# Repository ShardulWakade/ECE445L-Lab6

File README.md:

# Lab 6 Introduction to PCB Design

## Table of Contents

- [Lab 6 Introduction to PCB Design](#lab-6-introduction-to-pcb-design)
  - [Table of Contents](#table-of-contents)
  - [0 Repository Structure](#0-repository-structure)
    - [0.1 HW](#01-hw)
    - [0.2 SW](#02-sw)
    - [0.3 Resources](#03-resources)
    - [0.4 Git and Github](#04-git-and-github)
---

## 0 Repository Structure

The typical explanation for the repo structure. Lab specific instructions can be
found further below.

### 0.1 HW

The `hw` folder should contain your schematic and board files for your PCB or
circuits. In labs 1-5 and 10, you will be creating schematics for your circuit
in EAGLE. A setup tutorial can be found
[here](https://www.shawnvictor.net/autodesk-eagle.html).

### 0.2 SW

The `sw` folder should contain your application firmware and software written
for the lab. The `sw/inc` folder contains firmware drivers written for you by
Professor Valvano. Feel free to write your own (in fact, in some labs, you may
be required to write your own).

You can place any other source files in the `sw` folder. TAs will look at the
files you create and/or modify for software quality and for running your
project.

### 0.3 Resources

A couple files are provided in the Resources folder so you don't have to keep
searching for that one TI document. Some of them are immediately useful, like
the TM4C datasheet. Others may be useful for your final project, like the
TM4C_System_Design_Guidelines page.

### 0.4 Git and Github

We will extensively use Git and Github for managing lab projects. This makes it
easier for TAs to grade and help debug the project by allowing us to see commit
histories, maintain a common project structure, and likewise, it makes it easier
for students to collaborate with partners, merge different codebases, and to
debug their work by having a history of commits.

Two common ways of using Git and Github are [Github Desktop](https://desktop.github.com/) and the [command line](https://git-scm.com/downloads).
[Tutorials](https://dev.to/mollynem/git-github--workflow-fundamentals-5496) are also abundant on the net for you to peruse. We've provided a cheatsheet for git
in the Resources folder.

It is highly recommended to make the most out of Git, even if you've never used
it before. Version control will save you a lot of suffering, and tools like Git
or SVN are ubiquitous in the industry.

A gitignore file is added to the root of this repo that may prevent specific
files from being tagged to the repo. This are typically autogenerated output
files we don't care about, but sometimes other stuff (like .lib files) falls
through that we want. Feel free to modify if necessary.

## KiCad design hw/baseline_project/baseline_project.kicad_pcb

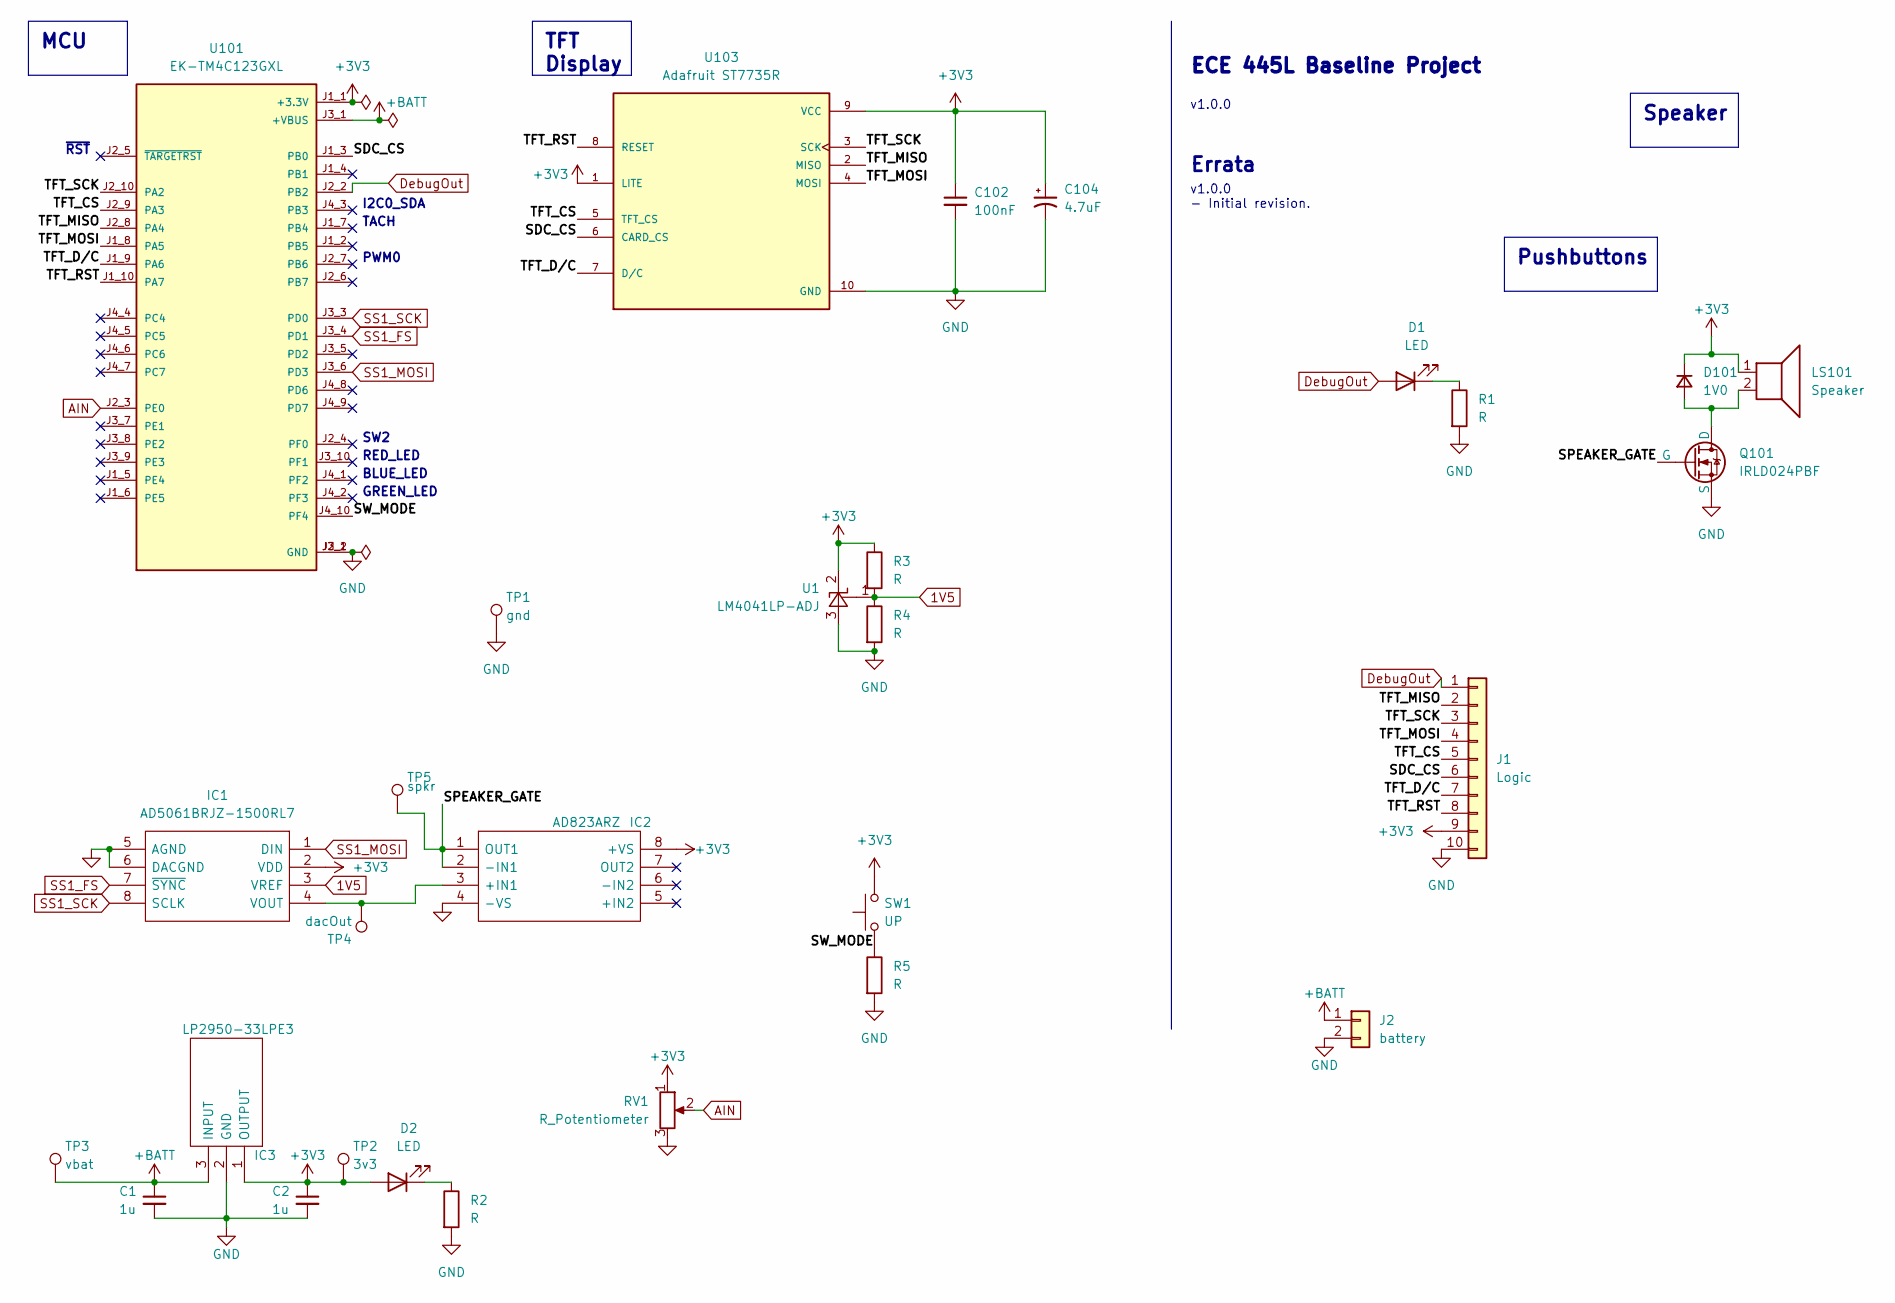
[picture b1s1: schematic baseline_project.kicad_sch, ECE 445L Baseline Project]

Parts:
C1, C2: 1u; C_1206_3216Metric
C102: 100nF; C_Axial_L5.1mm_D3.1mm_P15.00mm_Horizontal
C104: 4.7uF; CP_Axial_L10.0mm_D4.5mm_P15.00mm_Horizontal
D1, D2: LED; LED_D5.0mm
D101: 1V0; D_5W_P12.70mm_Horizontal
IC1: AD5061BRJZ-1500RL7; SOT65P280X145-8N; Mouser Part Number 584-AD5061BRJZ1500R7
IC2: AD823ARZ; SOIC127P600X175-8N; Mouser Part Number 584-AD823ARZ
IC3: LP2950-33LPE3; TO127P419X482X788-3P; Mouser Part Number 595-LP2950-33LPE3
J1: Logic; PinHeader_1x10_P2.54mm_Vertical
J2: battery; PinHeader_1x02_P2.54mm_Vertical
LS101: Speaker; PinHeader_1x02_P2.54mm_Vertical
Q101: IRLD024PBF; vishay_IRLD024PBF
R1, R2, R3, R4, R5: R; R_Axial_DIN0411_L9.9mm_D3.6mm_P12.70mm_Horizontal
RV1: R_Potentiometer; Potentiometer_Bourns_PTA3043_Single_Slide
SW1: UP; SW_PUSH_6mm
TP1: gnd; TestPoint_Bridge_Pitch7.62mm_Drill1.3mm
TP2: 3v3; TestPoint_Bridge_Pitch7.62mm_Drill1.3mm
TP3: vbat; TestPoint_Bridge_Pitch7.62mm_Drill1.3mm
TP4: dacOut; TestPoint_Bridge_Pitch7.62mm_Drill1.3mm
TP5: spkr; TestPoint_Bridge_Pitch7.62mm_Drill1.3mm
U1: LM4041LP-ADJ; TO-92_Inline
U101: EK-TM4C123GXL; ti_EKTM4C123GXL
U103: Adafruit ST7735R; adafruit_st7735r

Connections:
1V5: IC1.3 (VREF), R3.2, R4.1, U1.1 (FB)
+3V3: C2.1, C102.1, C104.1, D2.2 (A), D101.1 (K), IC1.2 (VDD), IC2.8 (+VS), IC3.1 (OUTPUT), J1.9, LS101.1, R3.1, RV1.1, SW1.2, TP2.1, U1.2 (K), U101.J1_1 (+3.3V), U103.1 (LITE), U103.9 (VCC)
+BATT: C1.1, IC3.3 (INPUT), J2.1, TP3.1, U101.J3_1 (+VBUS)
/SDC_CS: J1.6, U101.J1_3 (PB0), U103.6 (CARD_CS)
/SPEAKER_GATE: IC2.1 (OUT1), IC2.2 (-IN1), Q101.2 (G), TP5.1
/SW_MODE: R5.1, SW1.1, U101.J4_10 (PF4)
/TFT_CS: J1.5, U101.J2_9 (PA3), U103.5 (TFT_CS)
/TFT_D/C: J1.7, U101.J1_9 (PA6), U103.7 (D/C)
/TFT_MISO: J1.2, U101.J2_8 (PA4), U103.2 (MISO)
/TFT_MOSI: J1.4, U101.J1_8 (PA5), U103.4 (MOSI)
/TFT_RST: J1.8, U101.J1_10 (PA7), U103.8 (RESET)
/TFT_SCK: J1.3, U101.J2_10 (PA2), U103.3 (SCK)
AIN: RV1.2, U101.J2_3 (PE0)
DebugOut: D1.2 (A), J1.1, U101.J2_2 (PB2)
GND: C1.2, C2.2, C102.2, C104.2, IC1.5 (AGND), IC1.6 (DACGND), IC2.4 (-VS), IC3.2 (GND), J1.10, J2.2, Q101.3 (S), R1.2, R2.2, R4.2, R5.2, RV1.3, TP1.1, U1.3 (A), U101.J2_1 (GND), U101.J3_2 (GND), U103.10 (GND)
unnamed: D1.1 (K), R1.1
unnamed: D2.1 (K), R2.1
unnamed: D101.2 (A), LS101.2, Q101.1 (D)
unnamed: IC1.4 (VOUT), IC2.3 (+IN1), TP4.1
SS1_FS: IC1.7 (~SYNC), U101.J3_4 (PD1)
SS1_MOSI: IC1.1 (DIN), U101.J3_6 (PD3)
SS1_SCK: IC1.8 (SCLK), U101.J3_3 (PD0)

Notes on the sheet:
MCU
Speaker
Pushbuttons
TFT Display
v1.0.0 - Initial revision.
~{RST}
PWM0
TACH
ECE 445L Baseline Project
v1.0.0
Errata
BLUE_LED
I2C0_SDA
RED_LED
SW2
GREEN_LED

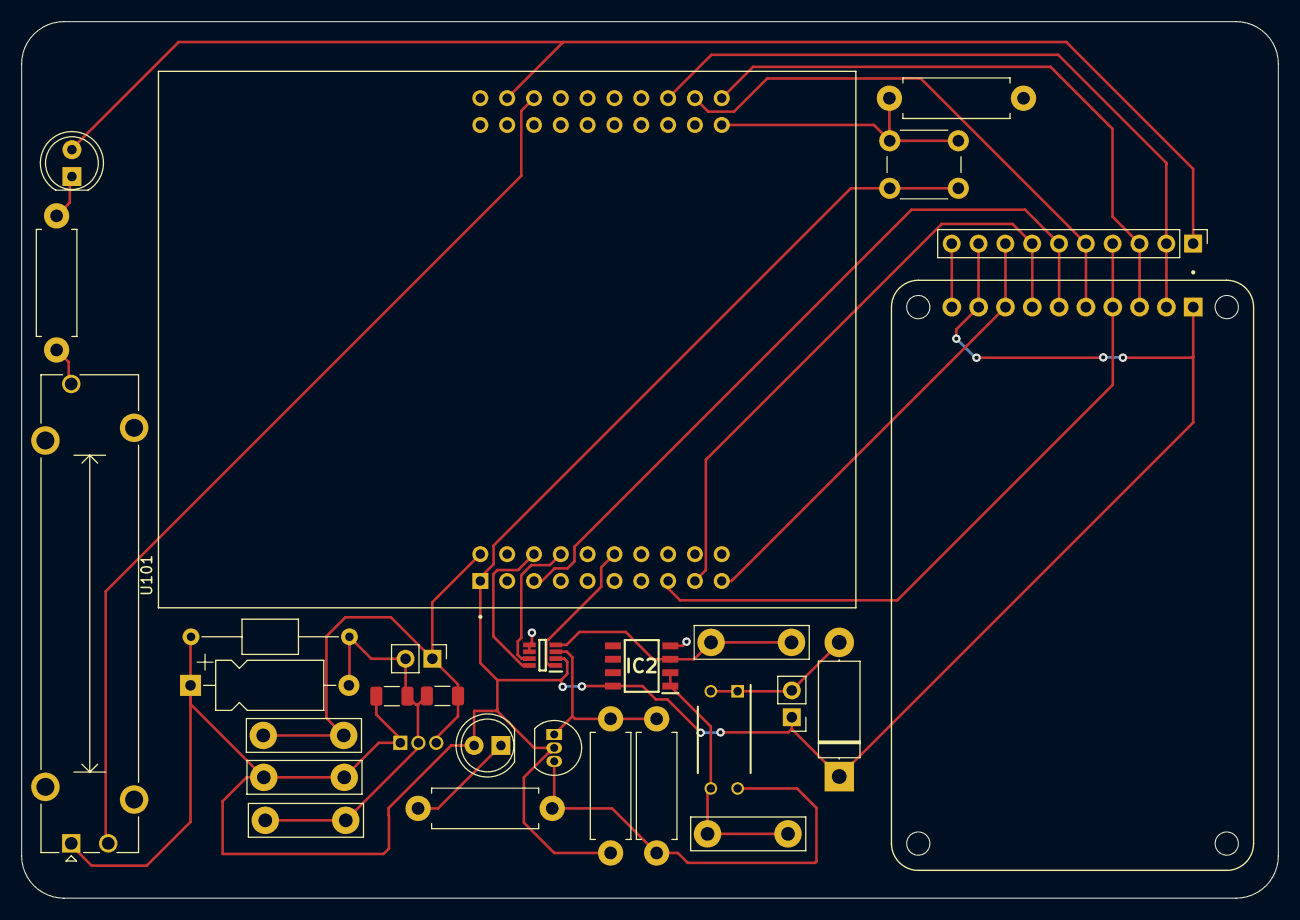
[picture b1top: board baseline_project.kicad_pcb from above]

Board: 2 copper layers, 119.0 x 83.0 mm, 29 parts (0 on the bottom side), 22 nets.

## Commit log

2022-02-26 Box Resource Walkthrough
2022-02-26 Box Resources
2022-02-26 EAGLE Tips
2022-02-26 Removed Jared's personal tips and tricks
2022-02-26 change software to a md file
2022-02-26 Made the software file a read me
2022-09-30 lowercase folders and initial Lab06.md
2022-09-30 bom instructions complete
2022-09-30 add eagle bom to csv python script
2022-09-30 more edits made to Lab06 document
2022-10-04 req doc w/o pictures
2022-10-04 lab6 doc edits
2022-10-05 only have sch left
2022-10-05 final Lab06.md
2022-10-05 part datasheets
2022-10-05 final temp revisions
2022-10-05 rename Lab06.md to README.md
2022-10-05 final revisions
2022-10-09 req doc adjust
2023-10-04 rm dep files
2023-10-04 add cleared bom, new lab doc
2023-10-04 rm submodules
2023-10-19 SchematicDone
